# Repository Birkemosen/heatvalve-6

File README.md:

# HeatValve-6

ESPHome firmware for the HeatValve-6 underfloor heating controller on ESP32-S3 with 6 DRV8215 I2C motor drivers.

This repository is now ESPHome-only. The legacy PlatformIO and ESP-IDF source tree has been removed.

## Repository Layout

```text
heatvalve-6/
├── heatvalve-6.yaml   # Main ESPHome firmware config
├── secrets.yaml       # Local secrets template (gitignored)
├── components/        # Custom ESPHome external components
│   ├── hv6_config_store/
│   ├── hv6_valve_controller/
│   └── hv6_zone_controller/
├── docs/
├── README.md
└── changelog.md
```

## What Is In The Firmware

- ESPHome on ESP-IDF
- 6-zone valve control with DRV8215 over I2C
- Custom C++ external components for config storage, valve control, and zone control
- Native ESPHome WiFi, API, OTA, web server, display, and climate entities
- DS18B20 1-Wire temperature sensors
- SSD1306 OLED support
- WS2812 status LED

## Hardware Mapping

| GPIO | Function |
|------|----------|
| GPIO1 | Motor current sense ADC |
| GPIO2 | DRV8215 nSLEEP |
| GPIO7 | DRV8215 nFAULT |
| GPIO8 | I2C SDA |
| GPIO9 | I2C SCL |
| GPIO12 | 1-Wire bus |
| GPIO48 | WS2812 status LED |

### DRV8215 Addresses

| Zone | Address |
|------|---------|
| 1 | 0x30 |
| 2 | 0x31 |
| 3 | 0x32 |
| 4 | 0x35 |
| 5 | 0x33 |
| 6 | 0x34 |

Only one motor should run at a time because current sensing is shared.

## Quick Start

1. Edit `secrets.yaml` with your WiFi, API, OTA, and optional MQTT values.
2. Replace the placeholder DS18B20 addresses in `heatvalve-6.yaml` after first discovery.
3. Build or deploy from the repo root.

Preferred workflow:

```bash
make build
make deploy
make logs
```

If you want USB flashing explicitly:

```bash
make deploy PORT=/dev/cu.usbmodemXXXX
```

If you want OTA to a specific host/IP:

```bash
make ota HOST=192.168.1.50
```

The `Makefile` automatically uses `.venv/bin/esphome` when present.

Direct ESPHome commands still work:

```bash
esphome run heatvalve-6.yaml
```

For config validation only:

```bash
esphome config heatvalve-6.yaml
```

## Notes

- The current firmware layout assumes the ESPHome config lives at the repository root.
- `secrets.yaml` is kept as a local template and remains gitignored.
- The repository has not been fully compile-tested yet after the migration.

## Documentation

- [docs/ARCHITECTURE.md](docs/ARCHITECTURE.md)
- [docs/ecodan_integration.md](docs/ecodan_integration.md)
- [docs/esp32-s3_ufh_pcb_solution.md](docs/esp32-s3_ufh_pcb_solution.md)
- [docs/schematics/rev3_wroom1/esp32_s3_wroom1_n16r8_controller.md](docs/schematics/rev3_wroom1/esp32_s3_wroom1_n16r8_controller.md)

## Inspiration & Credits

This project was inspired by and builds upon ideas from:

- [VdMot_Controller](https://github.com/Lenti84/VdMot_Controller) by Lenti84 — multiplexed motor control and current-based endstop detection for Homematic HmIP-VDMOT valve actuators
- [floor-heating-controller](https://github.com/nliaudat/floor-heating-controller) by nliaudat — BEMF analysis and trigger calculations for valve motor tachometry
- [Motor Controller Tachometer](https://yyao.ca/projects/motor_controller_tachometer/) by Yi Yao — back-EMF tachometer circuit design

## License

See [LICENSE](LICENSE) file.

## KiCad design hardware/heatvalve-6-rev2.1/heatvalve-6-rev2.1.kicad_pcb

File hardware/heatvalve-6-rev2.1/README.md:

# HeatValve-6 Rev 2.1 hardware

Editable KiCad 10 design for the USB-C-powered, six-channel DRV8837 HeatValve controller.

## Design state

- Schematic: complete first electrical-review revision; KiCad ERC reports 0 errors.
- PCB: compact four-layer 120 x 75 mm placement review with 128 electrical
  footprints, two M3 holes, an antenna notch, GND/+3V3 inner planes, and an
  intentionally unrouted ratsnest.
- Fabrication status: **not released**. Routing, mechanical confirmation, and final
  footprint/availability review are still required.
- PCB DRC: not current; KiCad CLI 10.0.3 aborts on both the original and updated
  board. See `drc.rpt` and rerun DRC in PCB Editor after routing.
- Prototype tuning: BEMF filter/gain/blanking, force threshold, engagement signature,
  and optional parallel shunt.

## Generate and validate

```bash
PYTHONPATH=/private/tmp/kicad_pydeps HOME=/private/tmp \
  python3 hardware/heatvalve-6-rev2.1/generate_kicad.py

kicad-cli sch erc \
  --output hardware/heatvalve-6-rev2.1/erc.rpt \
  hardware/heatvalve-6-rev2.1/heatvalve-6-rev2.1.kicad_sch

/Applications/KiCad/KiCad.app/Contents/Frameworks/Python.framework/Versions/3.9/bin/python3.9 \
  hardware/heatvalve-6-rev2.1/generate_pcb.py

kicad-cli pcb drc \
  --output hardware/heatvalve-6-rev2.1/drc.rpt \
  hardware/heatvalve-6-rev2.1/heatvalve-6-rev2.1.kicad_pcb
```

The committed `.kicad_sch` is usable without the Python generator dependency.

## Important design decisions

- Motors and logic operate from the MT2492-generated 3.3 V rail.
- Only one motor may run at a time.
- All DRV8837 ground returns meet at `SHUNT`; `RSH1` is the only normal return to system ground.
- `RSH1` is 1.0 ohm and INA180A1 provides x20 gain: 30 mA = 0.60 V,
  60 mA = 1.20 V, and 150 mA = 3.00 V. This preserves the pin-engagement peak.
- `R14`, `C13`, and `D5` provide additional ADC filtering and rail clamp protection.
- The hardware force-limit comparator reads the raw Kelvin shunt and remains effective if the ADC path saturates.
- Two 74HC4051 selectors connect only the active motor's A/B terminals to a
  shared differential BEMF front end. `ADC_BEMF` retains the raw waveform and
  `TACHO_EDGE` feeds PCNT after AC gain and hysteresis.
- Shunt ripple is not used as authoritative motion evidence. Firmware must qualify
  tacho edges against BEMF waveform, direction, switching blanking, and cadence.
- The latch powers up with `DRIVE_PERMIT` low and must be explicitly armed by firmware.
- Three OneWire connectors share GPIO42. The DNP I2C header uses GPIO1/GPIO2.
- Motor jacks use the center pair: pin 2 `MOT_A`, pin 3 `MOT_B`.

See `design-review.md` for calculations and release gates, and
`measurement-and-position.md` for engagement, modulation, endstop, and position logic.

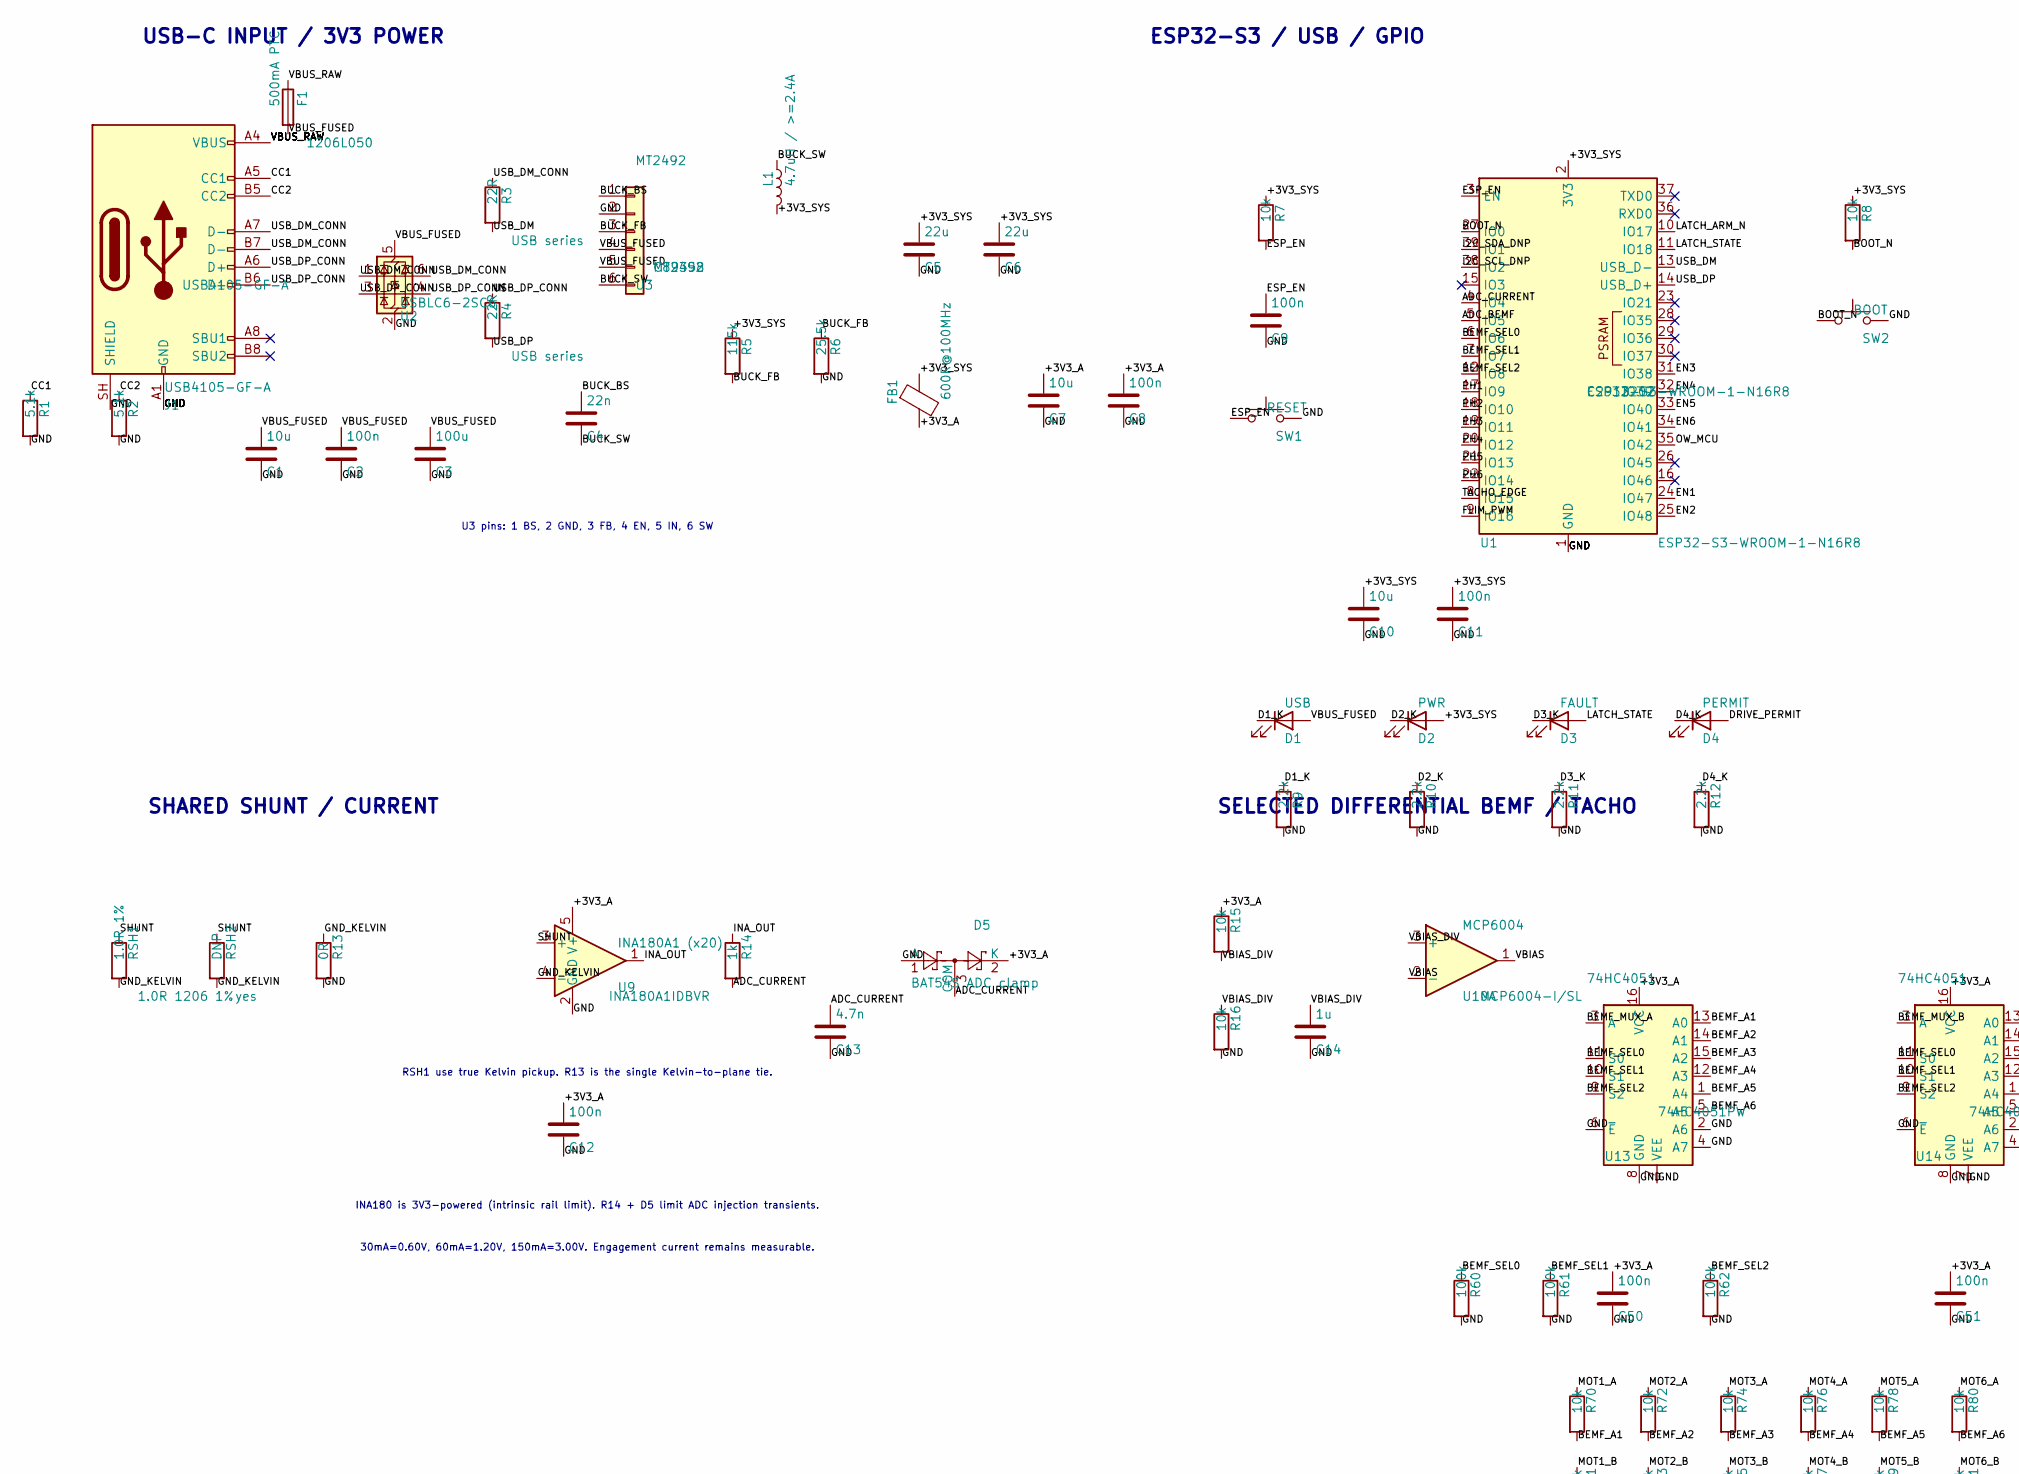
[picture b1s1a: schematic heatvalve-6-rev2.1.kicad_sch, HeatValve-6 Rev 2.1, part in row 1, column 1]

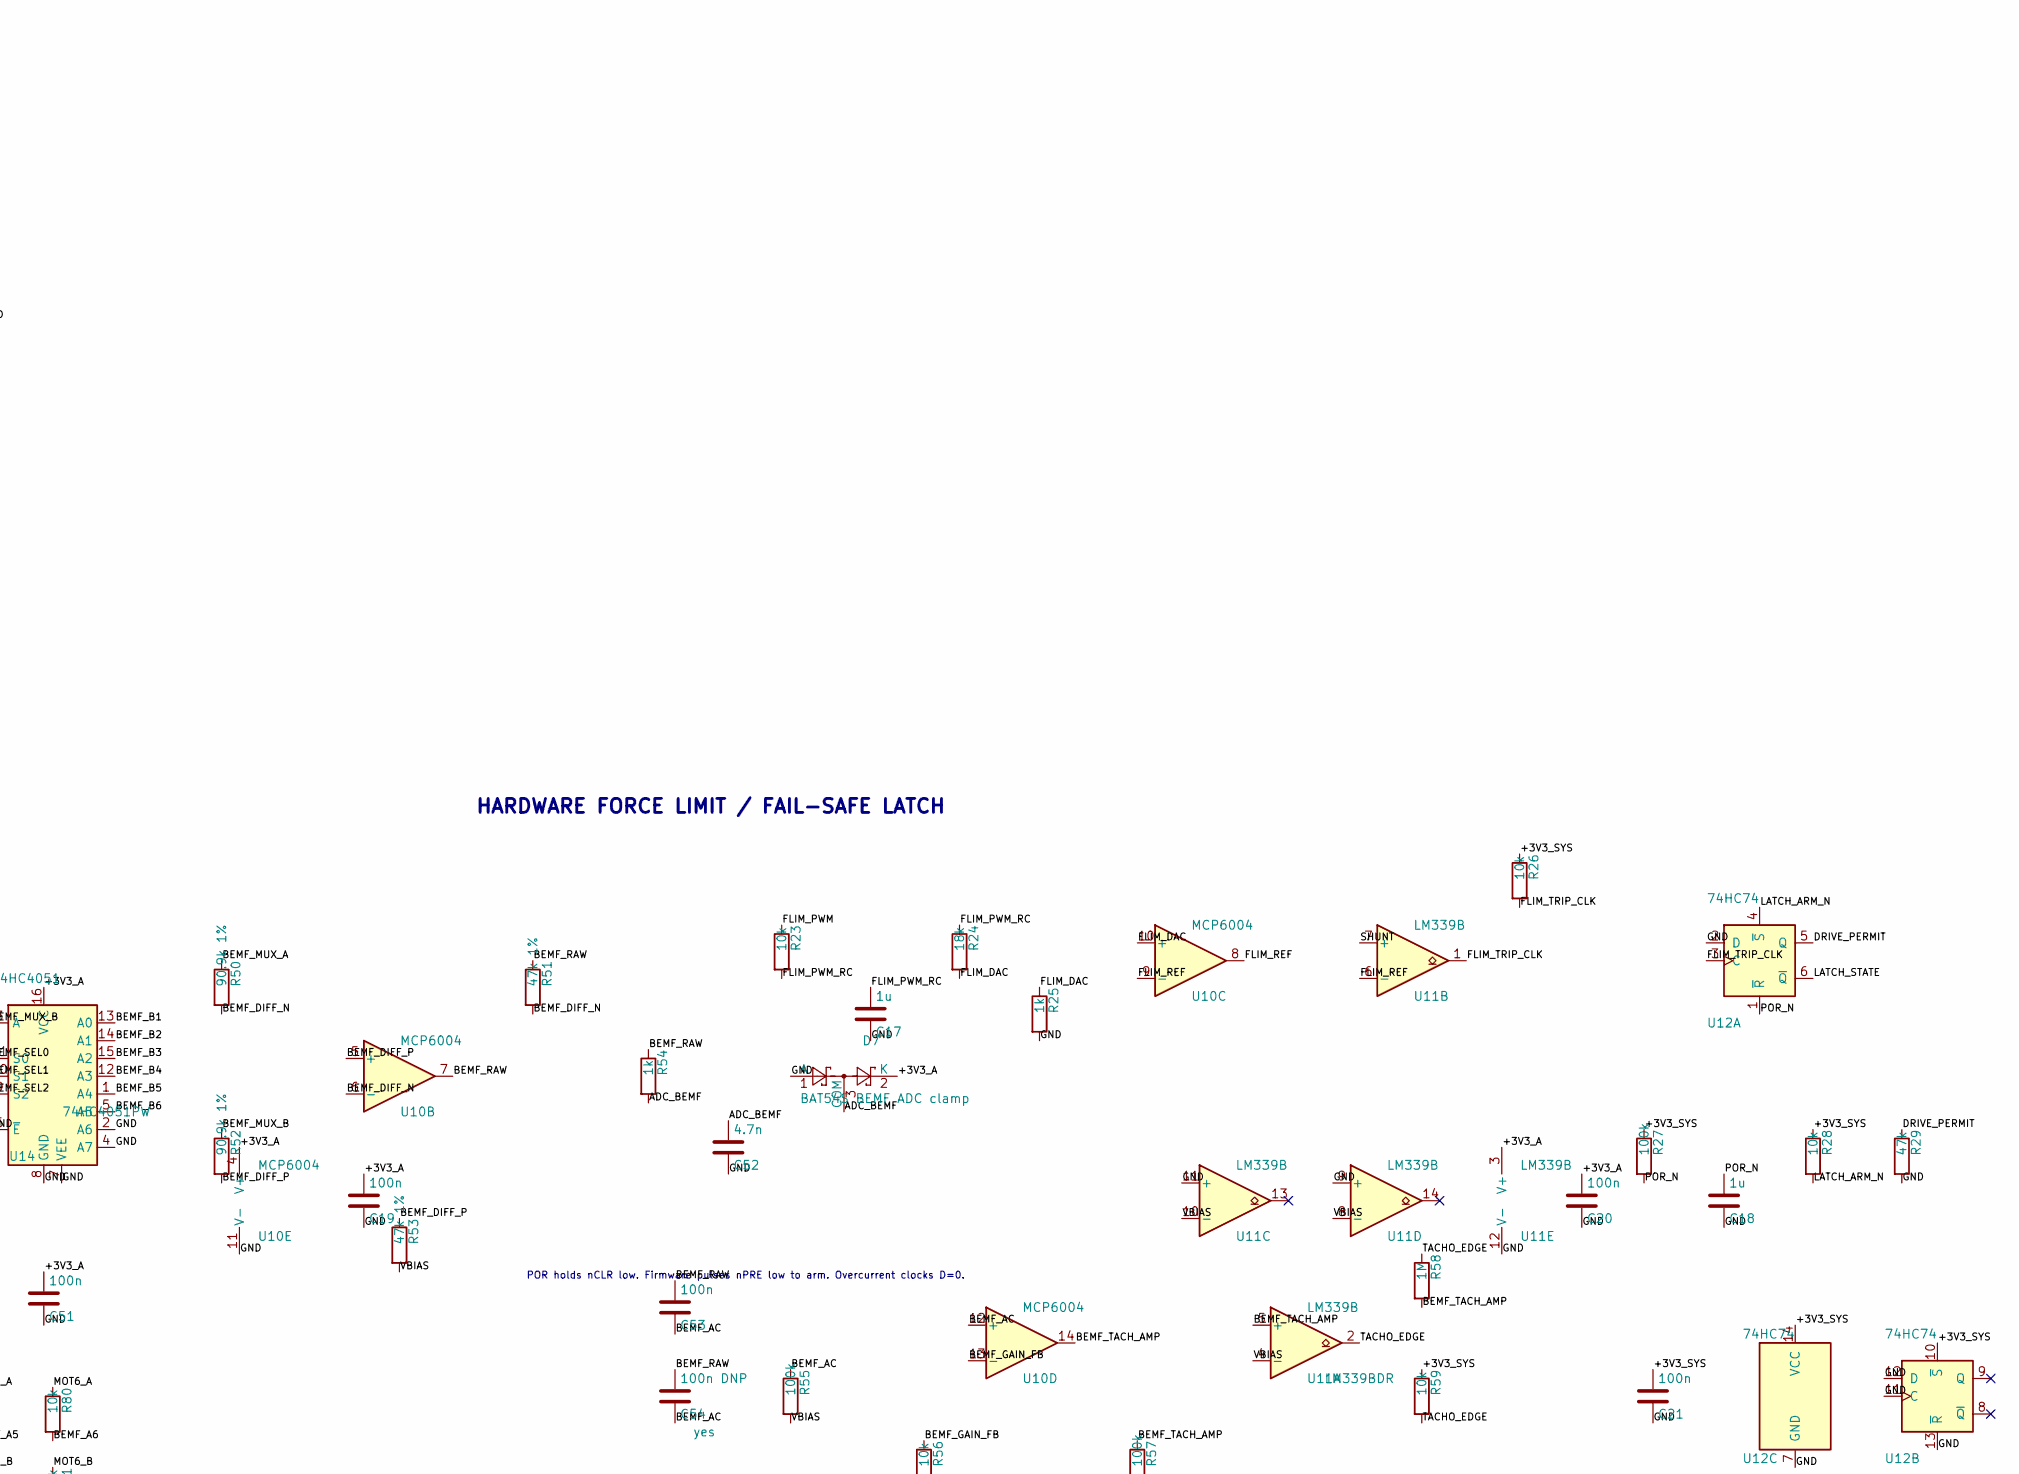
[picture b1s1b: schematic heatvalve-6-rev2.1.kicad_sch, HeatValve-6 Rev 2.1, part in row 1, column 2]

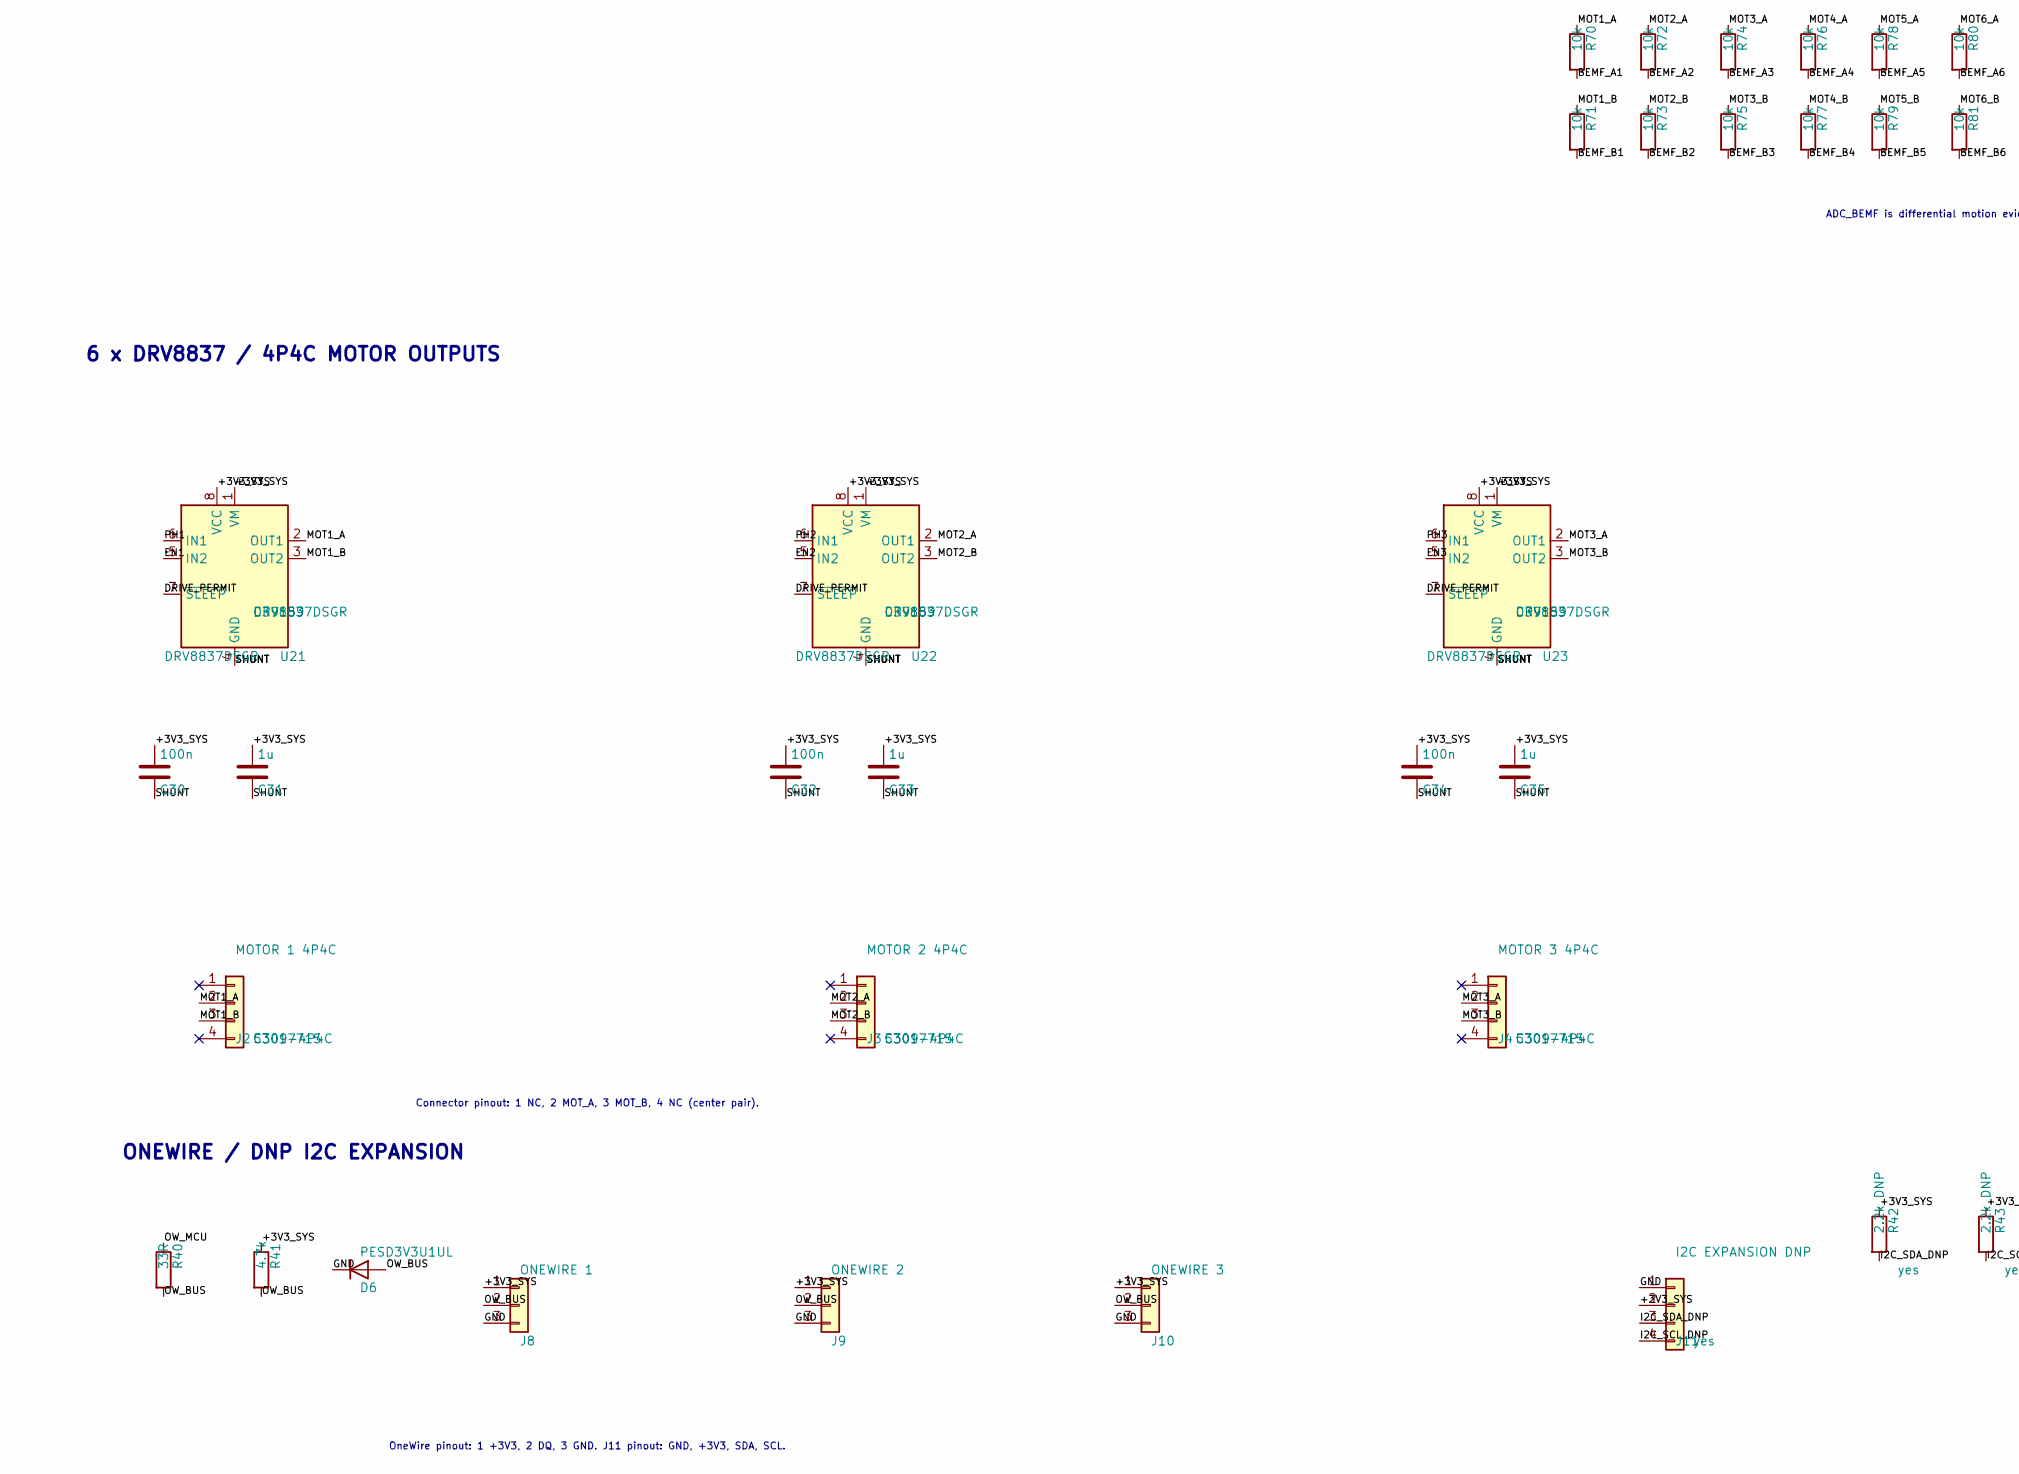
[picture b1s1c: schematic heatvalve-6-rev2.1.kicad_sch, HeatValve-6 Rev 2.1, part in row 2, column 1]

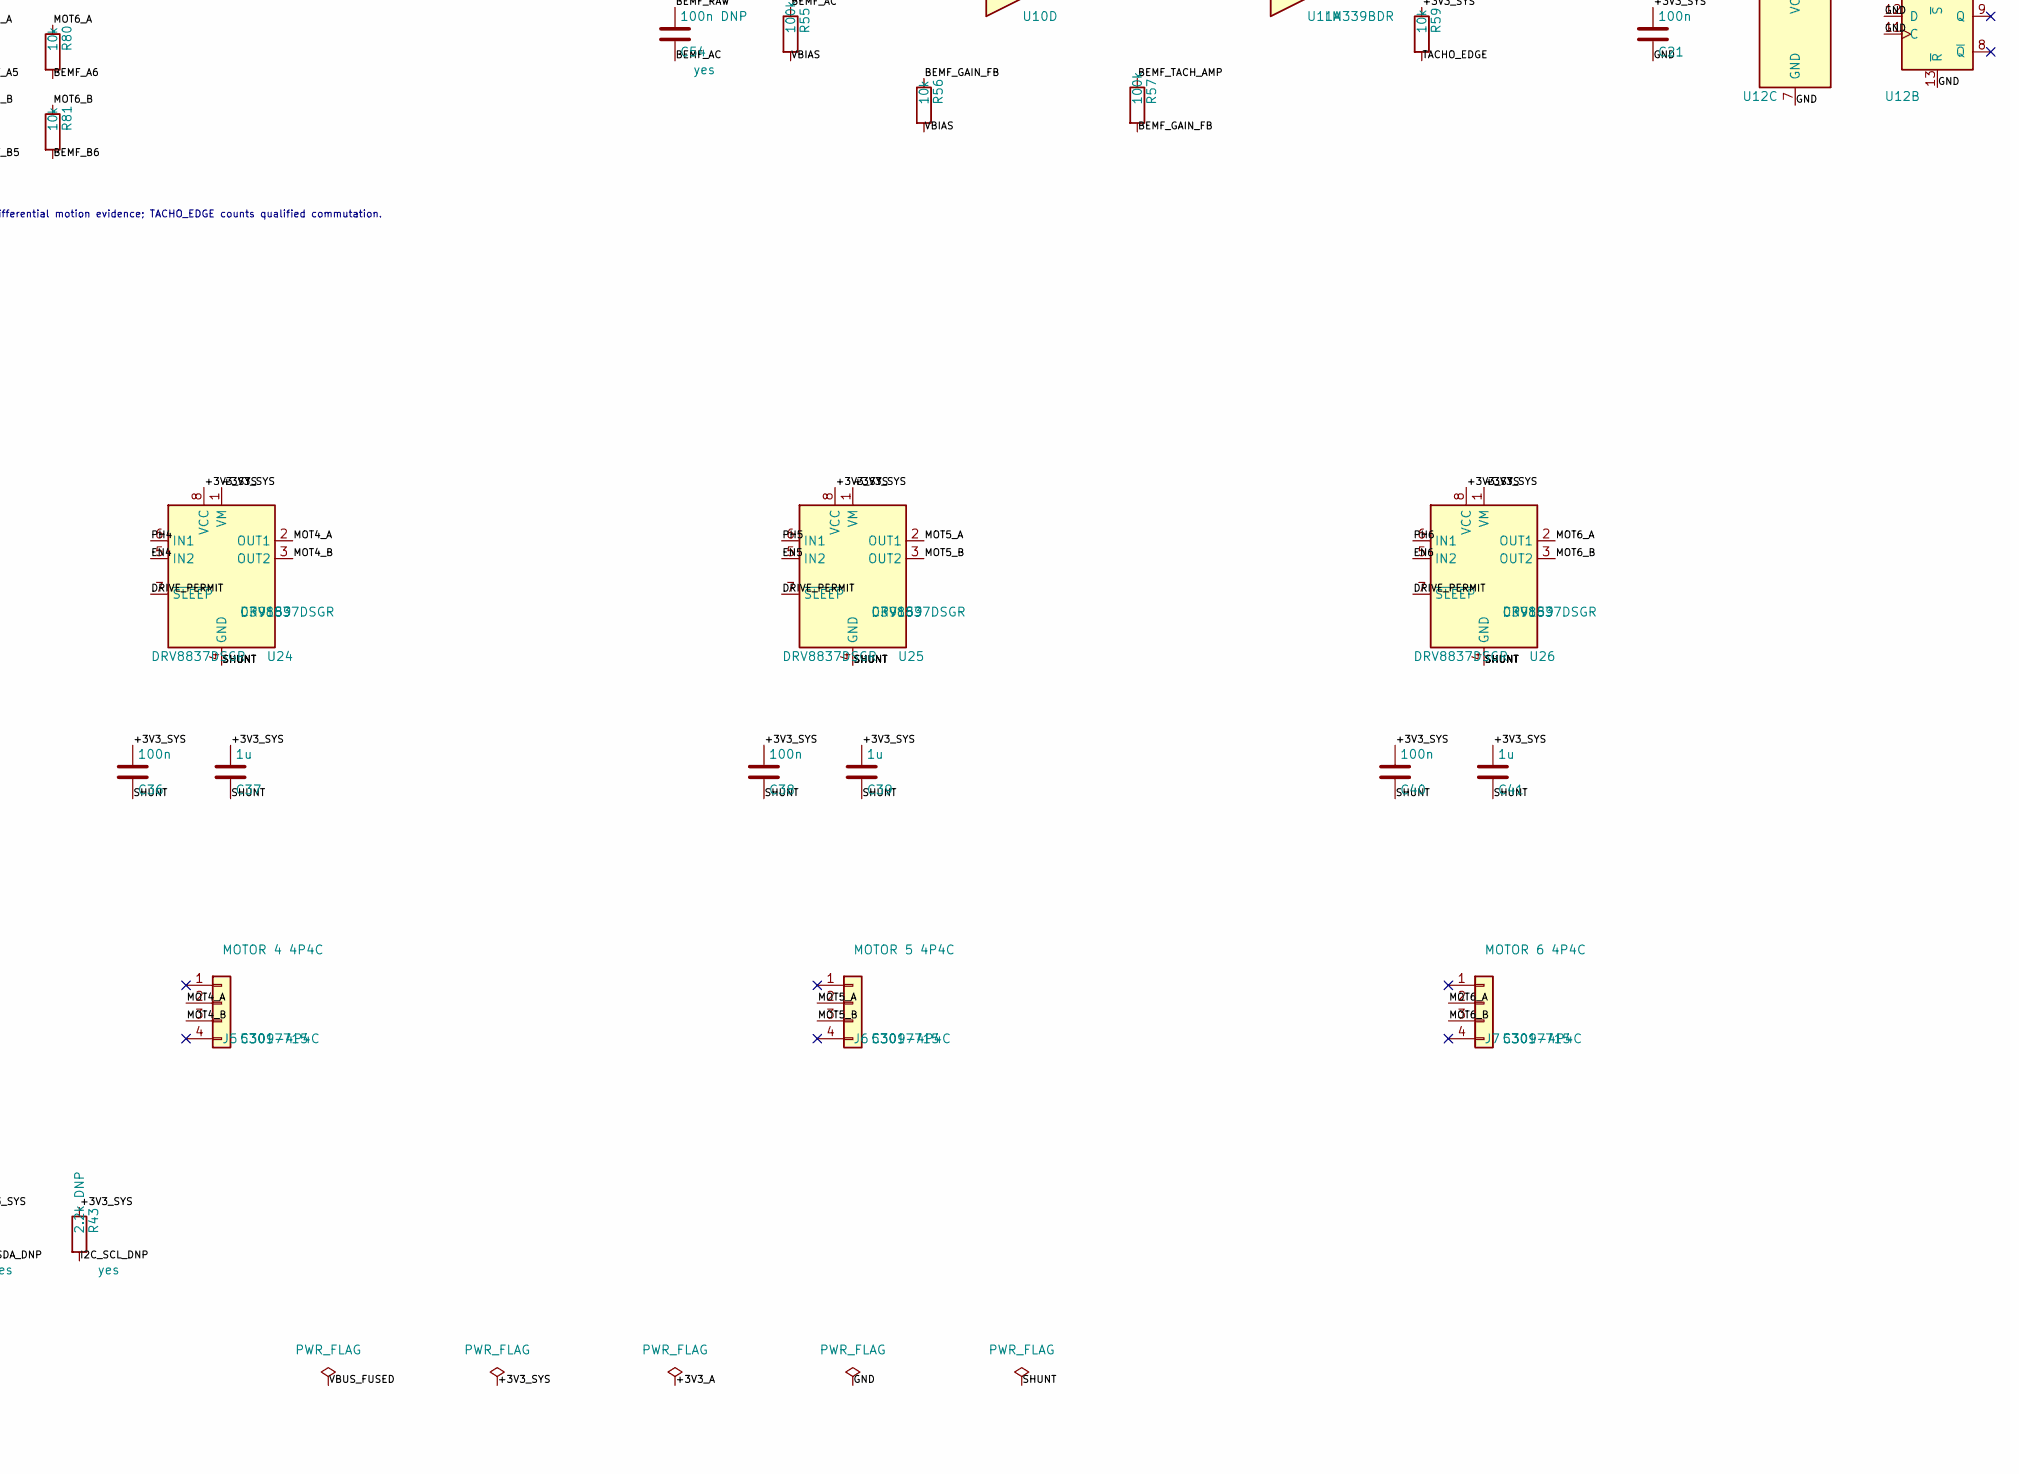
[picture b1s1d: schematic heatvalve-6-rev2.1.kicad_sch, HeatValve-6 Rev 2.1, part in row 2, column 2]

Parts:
C1: 10u; C_0603_1608Metric
C2, C8, C9, C11, C12, C19, C20, C21, C30, C32, C34, C36, C38, C40, C50, C51, C53: 100n; C_0603_1608Metric
C3: 100u; CP_Elec_6.3x7.7
C4: 22n; C_0603_1608Metric
C5, C6: 22u; C_0805_2012Metric
C7, C10: 10u; C_0805_2012Metric
C13, C52: 4.7n; C_0603_1608Metric
C14, C17, C18: 1u; C_0603_1608Metric
C31, C33, C35, C37, C39, C41: 1u; C_0805_2012Metric
C54: 100n DNP; C_0603_1608Metric
D1: USB; LED_0603_1608Metric
D2: PWR; LED_0603_1608Metric
D3: FAULT; LED_0603_1608Metric
D4: PERMIT; LED_0603_1608Metric
D5: BAT54S ADC clamp; SOT-23
D6: PESD3V3U1UL; D_SOD-323
D7: BAT54S BEMF ADC clamp; SOT-23
F1: 500mA PTC; Fuse_1206_3216Metric; MPN 1206L050
FB1: 600R@100MHz; L_0603_1608Metric_Pad1.05x0.95mm_HandSolder
J1: USB4105-GF-A; USB_C_Receptacle_GCT_USB4105-xx-A_16P_TopMnt_Horizontal; MPN USB4105-GF-A
J2: MOTOR 1 4P4C; RJ9_Evercom_5301-440xxx_Horizontal; MPN 5301-4P4C; LCSC C3097715
J3: MOTOR 2 4P4C; RJ9_Evercom_5301-440xxx_Horizontal; MPN 5301-4P4C; LCSC C3097715
J4: MOTOR 3 4P4C; RJ9_Evercom_5301-440xxx_Horizontal; MPN 5301-4P4C; LCSC C3097715
J5: MOTOR 4 4P4C; RJ9_Evercom_5301-440xxx_Horizontal; MPN 5301-4P4C; LCSC C3097715
J6: MOTOR 5 4P4C; RJ9_Evercom_5301-440xxx_Horizontal; MPN 5301-4P4C; LCSC C3097715
J7: MOTOR 6 4P4C; RJ9_Evercom_5301-440xxx_Horizontal; MPN 5301-4P4C; LCSC C3097715
J8: ONEWIRE 1; TerminalBlock_4Ucon_1x03_P3.50mm_Horizontal
J9: ONEWIRE 2; TerminalBlock_4Ucon_1x03_P3.50mm_Horizontal
J10: ONEWIRE 3; TerminalBlock_4Ucon_1x03_P3.50mm_Horizontal
J11: I2C EXPANSION DNP; PinHeader_1x04_P2.54mm_Vertical
L1: 4.7uH / >=2.4A; L_Wuerth_HCI-5040
R1, R2: 5.1k; R_0603_1608Metric
R3, R4: 22R; R_0603_1608Metric
R5: 115k; R_0603_1608Metric
R6: 25.5k; R_0603_1608Metric
R7, R8, R15, R16, R23, R26, R28, R56, R59, R70, R71, R72, R73, R74, R75, R76, R77, R78, R79, R80, R81: 10k; R_0603_1608Metric
R9, R10, R11, R12: 2.2k; R_0603_1608Metric
R13: 0R; R_0603_1608Metric
R14, R25, R54: 1k; R_0603_1608Metric
R24: 18k; R_0603_1608Metric
R27, R55, R57, R60, R61, R62: 100k; R_0603_1608Metric
R29: 47k; R_0603_1608Metric
R40: 33R; R_0603_1608Metric
R41: 4.7k; R_0603_1608Metric
R42, R43: 2.2k DNP; R_0603_1608Metric
R50, R52: 90.9k 1%; R_0603_1608Metric
R51, R53: 47k 1%; R_0603_1608Metric
R58: 1M; R_0603_1608Metric
RSH1: 1.0R 1%; R_1206_3216Metric; MPN 1.0R 1206 1%
RSH2: DNP; R_1206_3216Metric
SW1: RESET; SW_SPST_PTS810
SW2: BOOT; SW_SPST_PTS810
U1: ESP32-S3-WROOM-1-N16R8; ESP32-S3-WROOM-1; MPN ESP32-S3-WROOM-1-N16R8; LCSC C2913202
U2: USBLC6-2SC6; SOT-23-6
U3: MT2492; SOT-23-6; MPN MT2492; LCSC C89358
U9: INA180A1 (x20); SOT-23-5; MPN INA180A1IDBVR
U10: MCP6004; SOIC-14_3.9x8.7mm_P1.27mm; MPN MCP6004-I/SL
U11: LM339B; SOIC-14_3.9x8.7mm_P1.27mm; MPN LM339BDR
U12: 74HC74; SOIC-14_3.9x8.7mm_P1.27mm
U13, U14: 74HC4051; TSSOP-16_4.4x5mm_P0.65mm; MPN 74HC4051PW
U21, U22, U23, U24, U25, U26: DRV8837DSGR; WSON-8-1EP_2x2mm_P0.5mm_EP0.9x1.6mm; MPN DRV8837DSGR; LCSC C39159

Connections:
/+3V3_A: C7.1, C8.1, C12.1, C19.1, C20.1, C50.1, C51.1, D5.2 (K), D7.2 (K), FB1.2, R15.1, U9.5 (V+), U10.4 (V+), U11.3 (V+), U13.16 (VCC), U14.16 (VCC)
/+3V3_SYS: C5.1, C6.1, C10.1, C11.1, C21.1, C30.1, C31.1, C32.1, C33.1, C34.1, C35.1, C36.1, C37.1, C38.1, C39.1, C40.1, C41.1, D2.2 (A), FB1.1, J8.1, J9.1, J10.1, J11.2, L1.2, R5.1, R7.1, R8.1, R26.1, R27.1, R28.1, R41.1, R42.1, R43.1, R59.1, U1.2 (3V3), U12.10 (~S), U12.14 (VCC), U21.1 (VM), U21.8 (VCC), U22.1 (VM), U22.8 (VCC), U23.1 (VM), U23.8 (VCC), U24.1 (VM), U24.8 (VCC), U25.1 (VM), U25.8 (VCC), U26.1 (VM), U26.8 (VCC)
/ADC_BEMF: C52.1, D7.3 (COM), R54.2, U1.5 (IO5)
/ADC_CURRENT: C13.1, D5.3 (COM), R14.2, U1.4 (IO4)
/BEMF_A1: R70.2, U13.13 (A0)
/BEMF_A2: R72.2, U13.14 (A1)
/BEMF_A3: R74.2, U13.15 (A2)
/BEMF_A4: R76.2, U13.12 (A3)
/BEMF_A5: R78.2, U13.1 (A4)
/BEMF_A6: R80.2, U13.5 (A5)
/BEMF_AC: C53.2, C54.2, R55.1, U10.12 (+)
/BEMF_B1: R71.2, U14.13 (A0)
/BEMF_B2: R73.2, U14.14 (A1)
/BEMF_B3: R75.2, U14.15 (A2)
/BEMF_B4: R77.2, U14.12 (A3)
/BEMF_B5: R79.2, U14.1 (A4)
/BEMF_B6: R81.2, U14.5 (A5)
/BEMF_DIFF_N: R50.2, R51.2, U10.6 (-)
/BEMF_DIFF_P: R52.2, R53.1, U10.5 (+)
/BEMF_GAIN_FB: R56.1, R57.2, U10.13 (-)
/BEMF_MUX_A: R50.1, U13.3 (A)
/BEMF_MUX_B: R52.1, U14.3 (A)
/BEMF_RAW: C53.1, C54.1, R51.1, R54.1, U10.7
/BEMF_SEL0: R60.1, U1.6 (IO6), U13.11 (S0), U14.11 (S0)
/BEMF_SEL1: R61.1, U1.7 (IO7), U13.10 (S1), U14.10 (S1)
/BEMF_SEL2: R62.1, U1.12 (IO8), U13.9 (S2), U14.9 (S2)
/BEMF_TACH_AMP: R57.1, R58.2, U10.14, U11.5 (+)
/BOOT_N: R8.2, SW2.1, U1.27 (IO0)
/BUCK_BS: C4.1, U3.1
/BUCK_FB: R5.2, R6.1, U3.3
/BUCK_SW: C4.2, L1.1, U3.6
/CC1: J1.A5 (CC1), R1.1
/CC2: J1.B5 (CC2), R2.1
/D1_K: D1.1 (K), R9.1
/D2_K: D2.1 (K), R10.1
/D3_K: D3.1 (K), R11.1
/D4_K: D4.1 (K), R12.1
/DRIVE_PERMIT: D4.2 (A), R29.1, U12.5 (Q), U21.7 (~SLEEP), U22.7 (~SLEEP), U23.7 (~SLEEP), U24.7 (~SLEEP), U25.7 (~SLEEP), U26.7 (~SLEEP)
/EN1: U1.24 (IO47), U21.5 (IN2)
/EN2: U1.25 (IO48), U22.5 (IN2)
/EN3: U1.31 (IO38), U23.5 (IN2)
/EN4: U1.32 (IO39), U24.5 (IN2)
/EN5: U1.33 (IO40), U25.5 (IN2)
/EN6: U1.34 (IO41), U26.5 (IN2)
/ESP_EN: C9.1, R7.2, SW1.1, U1.3 (EN)
/FLIM_DAC: R24.2, R25.1, U10.10 (+)
/FLIM_PWM: R23.1, U1.9 (IO16)
/FLIM_PWM_RC: C17.1, R23.2, R24.1
/FLIM_REF: U10.8, U10.9 (-), U11.6 (-)
/FLIM_TRIP_CLK: R26.2, U11.1, U12.3 (C)
/GND: C1.2, C2.2, C3.2, C5.2, C6.2, C7.2, C8.2, C9.2, C10.2, C11.2, C12.2, C13.2, C14.2, C17.2, C18.2, C19.2, C20.2, C21.2, C50.2, C51.2, C52.2, D5.1 (A), D6.1 (K), D7.1 (A), J1.A1 (GND), J1.A12 (GND), J1.B1 (GND), J1.B12 (GND), J1.SH (SHIELD), J8.3, J9.3, J10.3, J11.1, R1.2, R2.2, R6.2, R9.2, R10.2, R11.2, R12.2, R13.2, R16.2, R25.2, R29.2, R60.2, R61.2, R62.2, SW1.2, SW2.2, U1.1 (GND), U1.40 (GND), U1.41 (GND), U2.2 (GND), U3.2, U9.2 (GND), U10.11 (V-), U11.9 (+), U11.11 (+), U11.12 (V-), U12.2 (D), U12.7 (GND), U12.11 (C), U12.12 (D), U12.13 (~R), U13.2 (A6), U13.4 (A7), U13.6 (~E), U13.7 (VEE), U13.8 (GND), U14.2 (A6), U14.4 (A7), U14.6 (~E), U14.7 (VEE), U14.8 (GND)
/GND_KELVIN: R13.1, RSH1.2, RSH2.2, U9.4 (-)
/I2C_SCL_DNP: J11.4, R43.2, U1.38 (IO2)
/I2C_SDA_DNP: J11.3, R42.2, U1.39 (IO1)
/INA_OUT: R14.1, U9.1
/LATCH_ARM_N: R28.2, U1.10 (IO17), U12.4 (~S)
/LATCH_STATE: D3.2 (A), U1.11 (IO18), U12.6 (~Q)
/MOT1_A: J2.2, R70.1, U21.2 (OUT1)
/MOT1_B: J2.3, R71.1, U21.3 (OUT2)
/MOT2_A: J3.2, R72.1, U22.2 (OUT1)
/MOT2_B: J3.3, R73.1, U22.3 (OUT2)
/MOT3_A: J4.2, R74.1, U23.2 (OUT1)
/MOT3_B: J4.3, R75.1, U23.3 (OUT2)
/MOT4_A: J5.2, R76.1, U24.2 (OUT1)
/MOT4_B: J5.3, R77.1, U24.3 (OUT2)
/MOT5_A: J6.2, R78.1, U25.2 (OUT1)
/MOT5_B: J6.3, R79.1, U25.3 (OUT2)
/MOT6_A: J7.2, R80.1, U26.2 (OUT1)
/MOT6_B: J7.3, R81.1, U26.3 (OUT2)
/OW_BUS: D6.2 (A), J8.2, J9.2, J10.2, R40.2, R41.2
/OW_MCU: R40.1, U1.35 (IO42)
/PH1: U1.17 (IO9), U21.6 (IN1)
/PH2: U1.18 (IO10), U22.6 (IN1)
/PH3: U1.19 (IO11), U23.6 (IN1)
/PH4: U1.20 (IO12), U24.6 (IN1)
/PH5: U1.21 (IO13), U25.6 (IN1)
/PH6: U1.22 (IO14), U26.6 (IN1)
/POR_N: C18.1, R27.2, U12.1 (~R)
/SHUNT: C30.2, C31.2, C32.2, C33.2, C34.2, C35.2, C36.2, C37.2, C38.2, C39.2, C40.2, C41.2, RSH1.1, RSH2.1, U9.3 (+), U11.7 (+), U21.4 (GND), U21.9 (GND), U22.4 (GND), U22.9 (GND), U23.4 (GND), U23.9 (GND), U24.4 (GND), U24.9 (GND), U25.4 (GND), U25.9 (GND), U26.4 (GND), U26.9 (GND)
/TACHO_EDGE: R58.1, R59.2, U1.8 (IO15), U11.2
/USB_DM: R3.2, U1.13 (USB_D-)
/USB_DM_CONN: J1.A7 (D-), J1.B7 (D-), R3.1, U2.1 (I/O1), U2.6 (I/O1)
/USB_DP: R4.2, U1.14 (USB_D+)
/USB_DP_CONN: J1.A6 (D+), J1.B6 (D+), R4.1, U2.3 (I/O2), U2.4 (I/O2)
/VBIAS: R53.2, R55.2, R56.2, U10.1, U10.2 (-), U11.4 (-), U11.8 (-), U11.10 (-)
/VBIAS_DIV: C14.1, R15.2, R16.1, U10.3 (+)
/VBUS_FUSED: C1.1, C2.1, C3.1, D1.2 (A), F1.2, U2.5 (VBUS), U3.4, U3.5
/VBUS_RAW: F1.1, J1.A4 (VBUS), J1.A9 (VBUS), J1.B4 (VBUS), J1.B9 (VBUS)

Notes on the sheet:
USB-C INPUT / 3V3 POWER
U3 pins: 1 BS, 2 GND, 3 FB, 4 EN, 5 IN, 6 SW
ESP32-S3 / USB / GPIO
SHARED SHUNT / CURRENT
RSH1 use true Kelvin pickup. R13 is the single Kelvin-to-plane tie.
INA180 is 3V3-powered (intrinsic rail limit). R14 + D5 limit ADC injection transients.
30mA=0.60V, 60mA=1.20V, 150mA=3.00V. Engagement current remains measurable.
SELECTED DIFFERENTIAL BEMF / TACHO
ADC_BEMF is differential motion evidence; TACHO_EDGE counts qualified commutation.
HARDWARE FORCE LIMIT / FAIL-SAFE LATCH
POR holds nCLR low. Firmware pulses nPRE low to arm. Overcurrent clocks D=0.
6 x DRV8837 / 4P4C MOTOR OUTPUTS
Connector pinout: 1 NC, 2 MOT_A, 3 MOT_B, 4 NC (center pair).
ONEWIRE / DNP I2C EXPANSION
OneWire pinout: 1 +3V3, 2 DQ, 3 GND. J11 pinout: GND, +3V3, SDA, SCL.

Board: 4 copper layers, 130 parts (0 on the bottom side), 88 nets, no tracks yet.

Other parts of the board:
H1, H2: M3; MountingHole_3.2mm_M3

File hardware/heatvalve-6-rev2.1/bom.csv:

"Refs","Value","Footprint","Qty","DNP","MPN","LCSC"
"C1","10u","Capacitor_SMD:C_0603_1608Metric","1","","",""
"C2,C8,C9,C11,C12,C19-C21,C30,C32,C34,C36,C38,C40,C50,C51,C53","100n","Capacitor_SMD:C_0603_1608Metric","17","","",""
"C3","100u","Capacitor_SMD:CP_Elec_6.3x7.7","1","","",""
"C4","22n","Capacitor_SMD:C_0603_1608Metric","1","","",""
"C5,C6","22u","Capacitor_SMD:C_0805_2012Metric","2","","",""
"C7,C10","10u","Capacitor_SMD:C_0805_2012Metric","2","","",""
"C13,C52","4.7n","Capacitor_SMD:C_0603_1608Metric","2","","",""
"C14,C17,C18","1u","Capacitor_SMD:C_0603_1608Metric","3","","",""
"C54","100n DNP","Capacitor_SMD:C_0603_1608Metric","1","yes","",""
"C31,C33,C35,C37,C39,C41","1u","Capacitor_SMD:C_0805_2012Metric","6","","",""
"D1","USB","LED_SMD:LED_0603_1608Metric","1","","",""
"D2","PWR","LED_SMD:LED_0603_1608Metric","1","","",""
"D3","FAULT","LED_SMD:LED_0603_1608Metric","1","","",""
"D4","PERMIT","LED_SMD:LED_0603_1608Metric","1","","",""
"D5","BAT54S ADC clamp","Package_TO_SOT_SMD:SOT-23","1","","",""
"D6","PESD3V3U1UL","Diode_SMD:D_SOD-323","1","","",""
"D7","BAT54S BEMF ADC clamp","Package_TO_SOT_SMD:SOT-23","1","","",""
"F1","500mA PTC","Fuse:Fuse_1206_3216Metric","1","","1206L050",""
"FB1","600R@100MHz","Inductor_SMD:L_0603_1608Metric_Pad1.05x0.95mm_HandSolder","1","","",""
"J1","USB4105-GF-A","Connector_USB:USB_C_Receptacle_GCT_USB4105-xx-A_16P_TopMnt_Horizontal","1","","USB4105-GF-A",""
"J2","MOTOR 1 4P4C","Connector_RJ:RJ9_Evercom_5301-440xxx_Horizontal","1","","5301-4P4C","C3097715"
"J3","MOTOR 2 4P4C","Connector_RJ:RJ9_Evercom_5301-440xxx_Horizontal","1","","5301-4P4C","C3097715"
"J4","MOTOR 3 4P4C","Connector_RJ:RJ9_Evercom_5301-440xxx_Horizontal","1","","5301-4P4C","C3097715"
"J5","MOTOR 4 4P4C","Connector_RJ:RJ9_Evercom_5301-440xxx_Horizontal","1","","5301-4P4C","C3097715"
"J6","MOTOR 5 4P4C","Connector_RJ:RJ9_Evercom_5301-440xxx_Horizontal","1","","5301-4P4C","C3097715"
"J7","MOTOR 6 4P4C","Connector_RJ:RJ9_Evercom_5301-440xxx_Horizontal","1","","5301-4P4C","C3097715"
"J8","ONEWIRE 1","TerminalBlock_4Ucon:TerminalBlock_4Ucon_1x03_P3.50mm_Horizontal","1","","",""
"J9","ONEWIRE 2","TerminalBlock_4Ucon:TerminalBlock_4Ucon_1x03_P3.50mm_Horizontal","1","","",""
"J10","ONEWIRE 3","TerminalBlock_4Ucon:TerminalBlock_4Ucon_1x03_P3.50mm_Horizontal","1","","",""
"J11","I2C EXPANSION DNP","Connector_PinHeader_2.54mm:PinHeader_1x04_P2.54mm_Vertical","1","yes","",""
"L1","4.7uH / >=2.4A","Inductor_SMD:L_Wuerth_HCI-5040","1","","",""
"R1,R2","5.1k","Resistor_SMD:R_0603_1608Metric","2","","",""
"R3,R4","22R","Resistor_SMD:R_0603_1608Metric","2","","",""
"R5","115k","Resistor_SMD:R_0603_1608Metric","1","","",""
"R6","25.5k","Resistor_SMD:R_0603_1608Metric","1","","",""
"R7,R8,R15,R16,R23,R26,R28,R56,R59,R70-R81","10k","Resistor_SMD:R_0603_1608Metric","21","","",""
"R9-R12","2.2k","Resistor_SMD:R_0603_1608Metric","4","","",""
"R13","0R","Resistor_SMD:R_0603_1608Metric","1","","",""
"R14,R25,R54","1k","Resistor_SMD:R_0603_1608Metric","3","","",""
"R27,R55,R57,R60-R62","100k","Resistor_SMD:R_0603_1608Metric","6","","",""
"R50,R52","90.9k 1%","Resistor_SMD:R_0603_1608Metric","2","","",""
"R51,R53","47k 1%","Resistor_SMD:R_0603_1608Metric","2","","",""
"R58","1M","Resistor_SMD:R_0603_1608Metric","1","","",""
"R24","18k","Resistor_SMD:R_0603_1608Metric","1","","",""
"R29","47k","Resistor_SMD:R_0603_1608Metric","1","","",""
"R40","33R","Resistor_SMD:R_0603_1608Metric","1","","",""
"R41","4.7k","Resistor_SMD:R_0603_1608Metric","1","","",""
"R42,R43","2.2k DNP","Resistor_SMD:R_0603_1608Metric","2","yes","",""
"RSH1","1.0R 1%","Resistor_SMD:R_1206_3216Metric","1","","1.0R 1206 1%",""
"RSH2","DNP","Resistor_SMD:R_1206_3216Metric","1","yes","",""
"SW1","RESET","Button_Switch_SMD:SW_SPST_PTS810","1","","",""
"SW2","BOOT","Button_Switch_SMD:SW_SPST_PTS810","1","","",""
"U1","ESP32-S3-WROOM-1-N16R8","RF_Module:ESP32-S3-WROOM-1","1","","ESP32-S3-WROOM-1-N16R8","C2913202"
"U2","USBLC6-2SC6","Package_TO_SOT_SMD:SOT-23-6","1","","",""
"U3","MT2492","Package_TO_SOT_SMD:SOT-23-6","1","","MT2492","C89358"
"U9","INA180A1 (x20)","Package_TO_SOT_SMD:SOT-23-5","1","","INA180A1IDBVR",""
"U10","MCP6004","Package_SO:SOIC-14_3.9x8.7mm_P1.27mm","1","","MCP6004-I/SL",""
"U11","LM339B","Package_SO:SOIC-14_3.9x8.7mm_P1.27mm","1","","LM339BDR",""
"U12","74HC74","Package_SO:SOIC-14_3.9x8.7mm_P1.27mm","1","","",""
"U13,U14","74HC4051","Package_SO:TSSOP-16_4.4x5mm_P0.65mm","2","","74HC4051PW",""
"U21-U26","DRV8837DSGR","Package_SON:WSON-8-1EP_2x2mm_P0.5mm_EP0.9x1.6mm","6","","DRV8837DSGR","C39159"
